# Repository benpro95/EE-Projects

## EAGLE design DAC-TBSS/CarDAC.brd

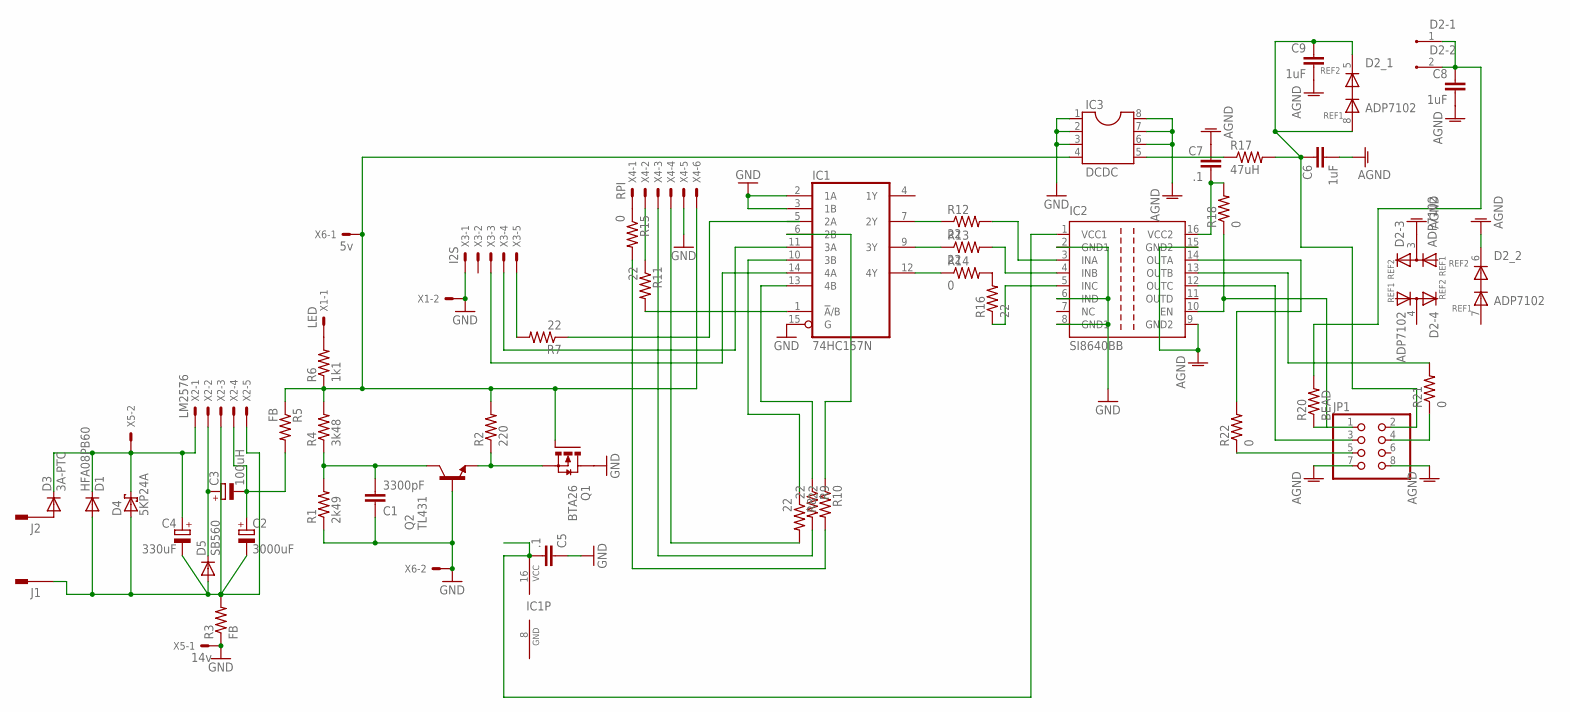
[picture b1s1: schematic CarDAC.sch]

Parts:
C1: 3300pF; C050-035X075
C2: 3000uF; E5-10,5
C3: 100uH; B45181C
C4: 330uF; E5-10,5
C5, C7: .1; C1210K
C6, C8, C9: 1uF; C1210K
D1: HFA08PB60; SOD57-10
D2: ADP7102; SO08
D3: 3A-PTC; SOD57-10
D4: 5KP24A; P6T15
D5: SB560; DO201-15
IC1: 74HC157N; DIL16
IC2: SI8640BB; SO-16DW
IC3: DCDC; DIL08
J1, J2: PIN2F061.040; F061.040
JP1: PINHD-2X4; 2X04
Q1: BTA26; TO247BV
Q2: TL431; TO92-EBC
R1: 2k49; 0309/10
R2: 220; 0309/10
R3: FB; 0309/10
R4: 3k48; 0309/10
R5: FB; 0309/12
R6: 1k1; 0309/10
R7, R9, R10, R11, R13: 22; 0309/12
R8, R16: 22; 0207/15
R12: 22; 0309/10
R14, R21: 0; 0207/15
R15: 0; 0309/12
R17: 47uH; 0309/10
R18, R22: 0; 0309/10
R20: BEAD; 0309/10
X1: LED; 22-23-2021
X2: LM2576; 22-23-2051
X3: I2S; 22-23-2051
X4: RPI; 22-23-2061
X5: 14v; 22-23-2021
X6: 5v; 22-23-2021

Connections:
AGND: C6.2, C7.1, C8.2, C9.2, D2.3 (K), D2.6 (REF2), IC2.9 (GND2), IC2.15 (GND2), IC3.6, IC3.7, IC3.8, JP1.7, JP1.8
GND: C1.1, C5.1, IC1.2 (1A), IC1.3 (1B), IC1.8 (GND), IC1.15 (G), IC2.2 (GND1), IC2.6 (IND), IC2.8 (GND1), IC3.1, IC3.2, IC3.3, Q1.D, Q2.B, R1.1, R3.1, X1.2, X3.1, X4.5, X5.1, X6.2
unnamed: Q1.S, Q2.E, R2.1
unnamed: IC3.4, Q1.G, R2.2, R4.2, R5.1, R6.1, X4.6, X6.1
unnamed: C1.2, Q2.C, R1.2, R4.1
unnamed: C4.+, D1.C, D3.C, D4.C, X2.1, X5.2
unnamed: D3.A, J2.A1, J2.A2
unnamed: C2.-, C4.-, D1.A, D4.A, D5.A, J1.A1, J1.A2, R3.2, X2.3, X2.5
unnamed: C3.+, D5.C, X2.2
unnamed: C2.+, C3.-, R5.2, X2.4
unnamed: R6.2, X1.1
unnamed: C5.2, IC1.16 (VCC), IC2.1 (VCC1)
unnamed: IC1.13 (4B), R9.1
unnamed: IC1.14 (4A), X3.3
unnamed: IC1.12 (4Y), R14.1
unnamed: IC1.10 (3B), R8.1
unnamed: IC1.11 (3A), X3.4
unnamed: IC1.6 (2B), R10.1
unnamed: IC1.5 (2A), R7.1
unnamed: R7.2, X3.5
unnamed: R10.2, R15.2
unnamed: IC1.1 (!A!/B), R11.2
unnamed: R9.2, X4.3
unnamed: R8.2, X4.4
unnamed: R11.1, X4.2
unnamed: IC1.7 (2Y), R12.1
unnamed: IC1.9 (3Y), R13.1
unnamed: R15.1, X4.1
unnamed: IC2.3 (INA), R12.2
unnamed: IC2.4 (INB), R13.2
unnamed: IC2.5 (INC), R16.1
unnamed: IC3.5, R17.1
unnamed: R14.2, R16.2
unnamed: C6.1, C9.1, D2.5 (REF2), D2.8 (REF1), JP1.2, R17.2
unnamed: IC2.10 (EN), JP1.1, R18.1, R20.1
unnamed: C8.1, D2.1 (K), D2.2 (K), R20.2
unnamed: IC2.12 (OUTC), JP1.3
unnamed: IC2.13 (OUTB), R21.2
unnamed: IC2.14 (OUTA), R22.2
unnamed: JP1.5, R22.1
unnamed: C7.2, IC2.16 (VCC2), R18.2
unnamed: JP1.4, R21.1

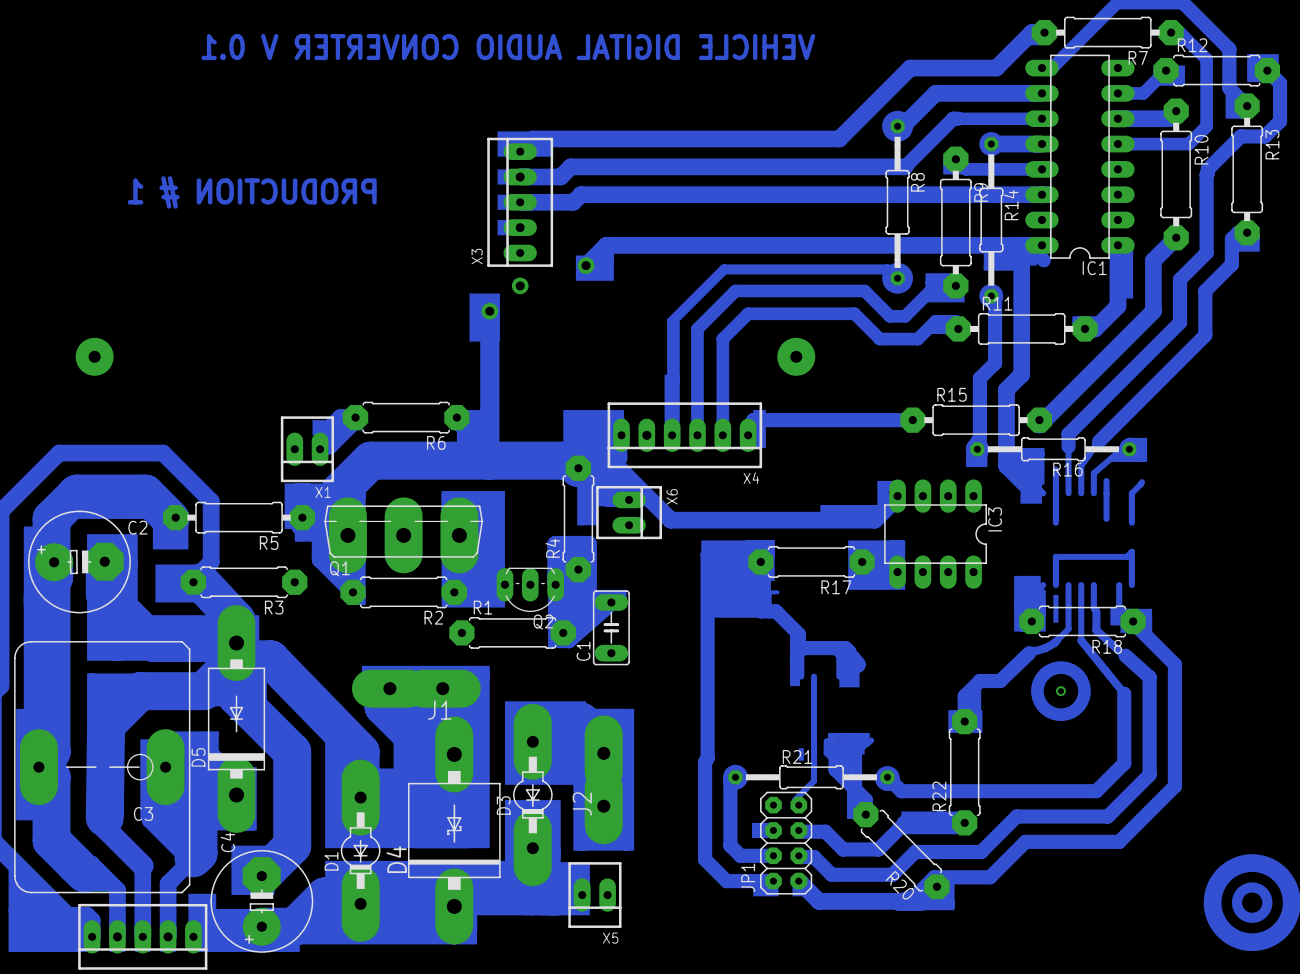
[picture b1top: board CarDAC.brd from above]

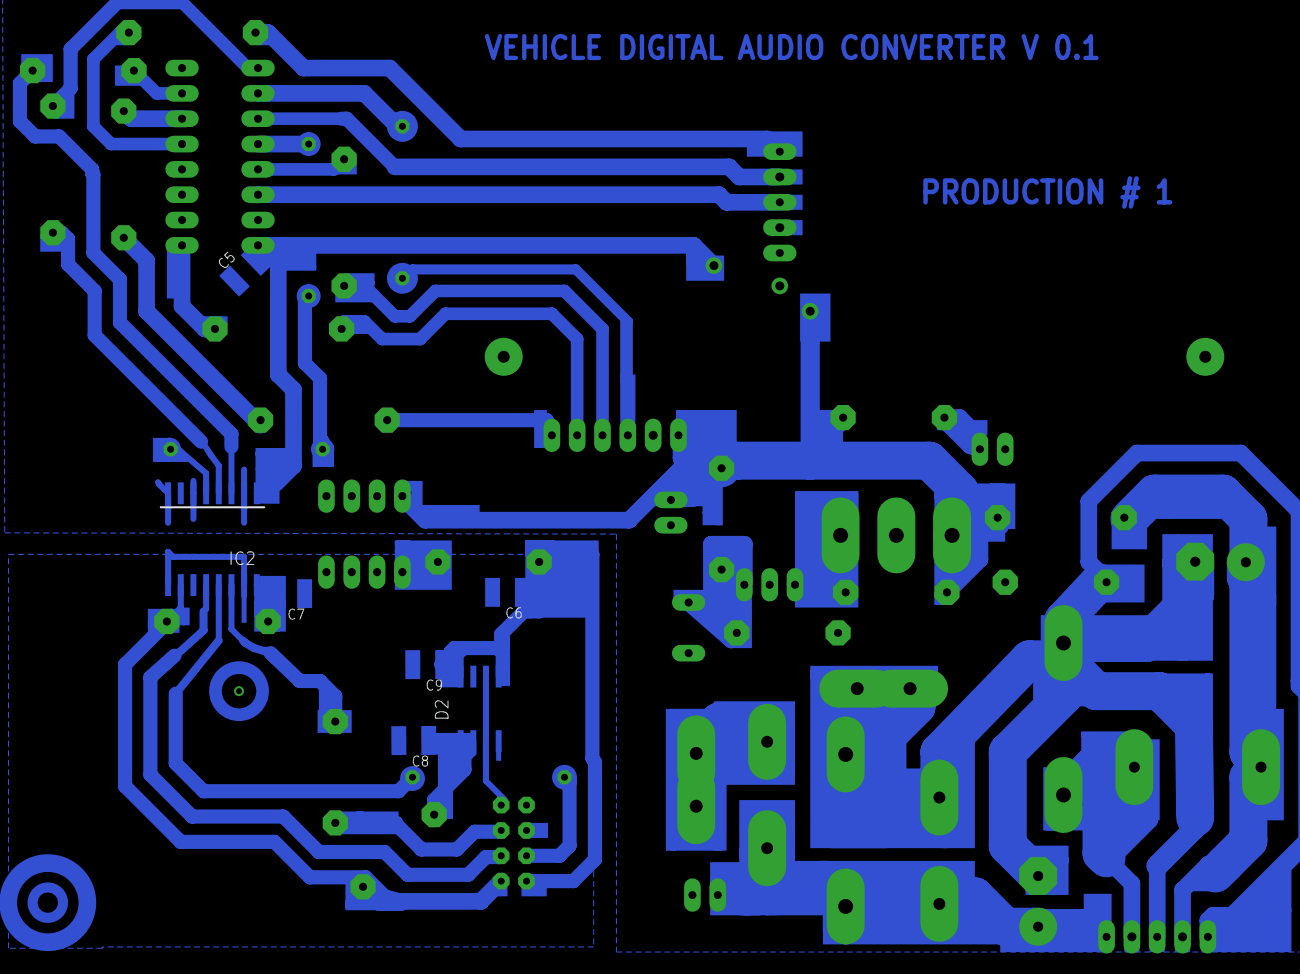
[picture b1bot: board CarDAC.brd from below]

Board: 2 copper layers, 49 parts (7 on the bottom side), 42 nets.

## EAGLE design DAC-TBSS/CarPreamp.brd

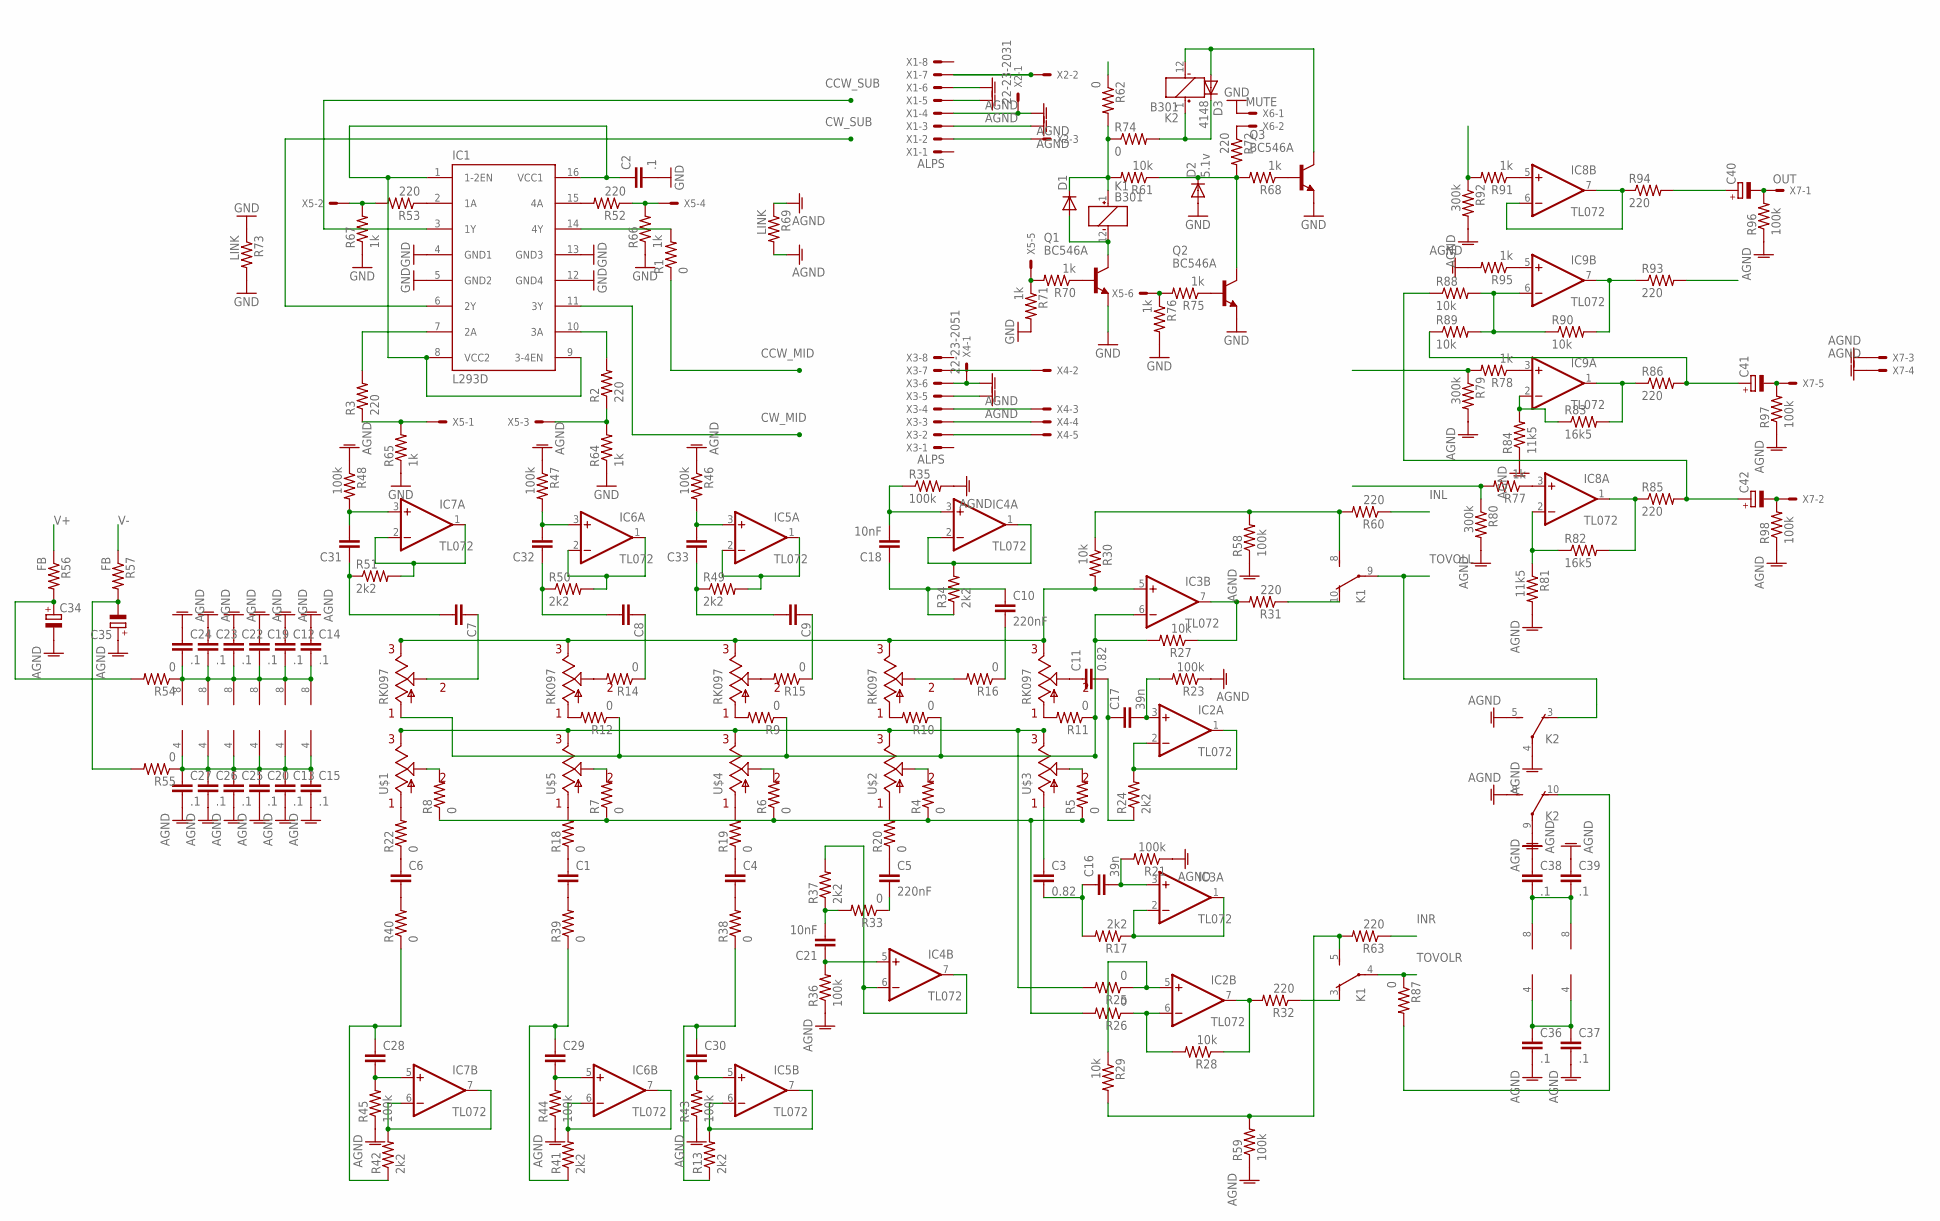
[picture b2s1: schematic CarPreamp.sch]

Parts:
C1, C4, C6, C7, C8, C9, C28, C29, C30, C31, C32, C33: C-EU050-035X075; C050-035X075
C2, C12, C13, C14, C15, C19, C20, C22, C23, C24, C25, C26, C27, C36, C37, C38, C39: .1; C1210
C3, C11: 0.82; C075-032X103
C5, C10: 220nF; C050-035X075
C16, C17: 39n; C050-035X075
C18, C21: 10nF; C050-035X075
C34, C35, C40, C41, C42: CPOL-EUE3.5-8; E3,5-8
D1: 1N4148DO35-10; DO35-10
D2: 5.1v; DO35-10
D3: 4148; DO35-10
IC1: L293D; DIL16
IC2, IC3, IC4, IC5, IC6, IC7, IC8, IC9: TL072; DIL08
K1, K2: B301; TXD2
Q1, Q2, Q3: BC546A; TO92-EBC
R1, R74: 0; 0309/12
R2: 220; 0309/12
R3: 220; 0207/15
R4, R5, R6, R7, R8, R9, R10, R11, R12, R14, R15, R16, R18, R19, R20, R22: 0; 0207/7
R13, R17, R24, R34, R37, R41, R42, R49, R50, R51: 2k2; 0207/7
R21, R23, R35, R36, R43, R44, R45, R46, R47, R48, R58, R59, R96, R97, R98: 100k; 0207/7
R25, R38, R39, R40, R87: 0; 0207/10
R26: 0; 0207/12
R27, R28, R61: 10k; R1210
R29, R88, R89, R90: 10k; 0207/7
R30: 10k; 0207/12
R31, R60, R63, R85, R86, R93, R94: 220; 0207/7
R32: 220; 0207/12
R33, R54, R62: 0; 0309/10
R52, R53: 220; 0309/10
R55: 0; 0411/15
R56, R57: FB; 0309/12
R64, R65, R66, R67, R68, R70, R71: 1k; R1210
R69: LINK; 0309/12
R72: 220; R1210
R73: LINK; 0309/10
R75, R76: 1k; 0309/10
R77, R78, R91: 1k; 0207/7
R79, R80, R92: 300k; 0207/7
R81, R84: 11k5; 0207/7
R82, R83: 16k5; 0207/7
R95: 1k; 0207/10
U$1, U$2, U$3, U$4, U$5: RK097; RK097-DUAL-ELEMENT
X1, X3: ALPS; 22-23-2081
X2: 22-23-2031
X4: 22-23-2051
X5: 22-23-2061
X6: MUTE; 22-23-2021
X7: OUT; 22-23-2051

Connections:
5V: C2.1, IC1.1 (1-2EN), IC1.8 (VCC2), IC1.9 (3-4EN), IC1.16 (VCC1), R62.1
AGND: C12.1, C13.2, C14.1, C15.2, C19.1, C20.2, C22.1, C23.1, C24.1, C25.2, C26.2, C27.2, C34.-, C35.+, C36.2, C37.2, C38.1, C39.1, K2.4, K2.5 (S), K2.8 (S), K2.9, R21.1, R23.1, R35.2, R36.1, R43.1, R44.1, R45.1, R46.1, R47.1, R48.1, R58.1, R59.1, R69.1, R69.2, R79.2, R80.2, R81.2, R84.1, R92.2, R95.2, R96.1, R97.1, R98.1, X1.3, X1.4, X1.5, X1.6, X2.1, X3.5, X3.6, X4.1, X7.3, X7.4
CCW_MID: R1.1
CCW_SUB: IC1.3 (1Y)
CW_MID: IC1.11 (3Y)
CW_SUB: IC1.6 (2Y)
GND: C2.2, D2.A, IC1.4 (GND1), IC1.5 (GND2), IC1.12 (GND4), IC1.13 (GND3), Q1.E, Q2.E, Q3.E, R64.1, R65.1, R66.1, R67.1, R71.2, R73.1, R73.2, R76.2, X6.1
INL: R60.1
INR: R63.1
unnamed: IC1.14 (4Y), R1.2
unnamed: X3.2, X4.5
unnamed: X3.3, X4.4
unnamed: IC1.7 (2A), R3.2
unnamed: IC1.15 (4A), R52.2
unnamed: X1.2, X2.3
unnamed: X1.7, X2.2
unnamed: IC1.10 (3A), R2.2
unnamed: X3.7, X4.2
unnamed: R25.2, U$1.P$4 (E1), U$2.P$4 (E1), U$3.P$4 (E1), U$4.P$4 (E1), U$5.P$4 (E1)
unnamed: IC3.5 (+IN), R30.2, U$1.P$3 (E), U$2.P$3 (E), U$3.P$3 (E), U$4.P$3 (E), U$5.P$3 (E)
unnamed: X3.4, X4.3
unnamed: R5.2, U$3.P$6 (S1)
unnamed: R6.2, U$4.P$6 (S1)
unnamed: R7.2, U$5.P$6 (S1)
unnamed: R8.2, U$1.P$6 (S1)
unnamed: R4.1, R5.1, R6.1, R7.1, R8.1, R26.2
unnamed: R16.2, U$2.P$5 (S)
unnamed: R4.2, U$2.P$6 (S1)
unnamed: R9.2, U$4.P$1 (A)
unnamed: R10.2, U$2.P$1 (A)
unnamed: R11.2, U$3.P$1 (A)
unnamed: R12.2, U$5.P$1 (A)
unnamed: IC7.6 (-IN), IC7.7 (OUT), R42.2
unnamed: IC3.6 (-IN), R9.1, R10.1, R11.1, R12.1, R27.2, U$1.P$1 (A)
unnamed: R14.2, U$5.P$5 (S)
unnamed: R15.2, U$4.P$5 (S)
unnamed: C11.1, U$3.P$5 (S)
unnamed: R18.2, U$5.P$2 (A1)
unnamed: R19.2, U$4.P$2 (A1)
unnamed: R20.2, U$2.P$2 (A1)
unnamed: C3.1, U$3.P$2 (A1)
unnamed: R22.2, U$1.P$2 (A1)
unnamed: C1.1, R18.1
unnamed: IC6.6 (-IN), IC6.7 (OUT), R41.2
unnamed: C4.1, R19.1
unnamed: C5.1, R20.1
unnamed: C6.1, R22.1
unnamed: C7.1, U$1.P$5 (S)
unnamed: C8.1, R14.1
unnamed: C9.1, R15.1
unnamed: C10.2, R16.1
unnamed: IC5.6 (-IN), IC5.7 (OUT), R13.2
unnamed: IC2.5 (+IN), R25.1, R29.1
unnamed: IC2.6 (-IN), R26.1, R28.2
unnamed: IC3.7 (OUT), R27.1, R31.2
unnamed: IC2.7 (OUT), R28.1, R32.2
unnamed: IC4.1 (OUT), IC4.2 (-IN), R34.2
unnamed: C10.1, C18.1, R34.1
unnamed: IC4.6 (-IN), IC4.7 (OUT), R37.2
unnamed: IC2.1 (OUT), IC2.2 (-IN), R24.2
unnamed: IC3.1 (OUT), IC3.2 (-IN), R17.1
unnamed: C16.2, IC3.3 (+IN), R21.2
unnamed: C3.2, C16.1, R17.2
unnamed: C17.2, IC2.3 (+IN), R23.2
unnamed: C11.2, C17.1, R24.1
unnamed: C5.2, R33.1
unnamed: C18.2, IC4.3 (+IN), R35.1
unnamed: C21.2, R33.2, R37.1
unnamed: C21.1, IC4.5 (+IN), R36.2
unnamed: C12.2, C14.2, C19.2, C22.2, C23.2, C24.2, IC2.8 (V+), IC3.8 (V+), IC4.8 (V+), IC5.8 (V+), IC6.8 (V+), IC7.8 (V+), R54.1
unnamed: C28.2, IC7.5 (+IN), R45.2
unnamed: C29.2, IC6.5 (+IN), R44.2
unnamed: C30.2, IC5.5 (+IN), R43.2
unnamed: C28.1, R40.1, R42.1
unnamed: C13.1, C15.1, C20.1, C25.1, C26.1, C27.1, IC2.4 (V-), IC3.4 (V-), IC4.4 (V-), IC5.4 (V-), IC6.4 (V-), IC7.4 (V-), R55.1
unnamed: C4.2, R38.2
unnamed: C1.2, R39.2
unnamed: C6.2, R40.2
unnamed: C29.1, R39.1, R41.1
unnamed: C30.1, R13.1, R38.1
unnamed: IC7.1 (OUT), IC7.2 (-IN), R51.2
unnamed: IC6.1 (OUT), IC6.2 (-IN), R50.2
unnamed: IC5.1 (OUT), IC5.2 (-IN), R49.2
unnamed: C7.2, C31.1, R51.1
unnamed: C8.2, C32.1, R50.1
unnamed: C9.2, C33.1, R49.1
unnamed: C31.2, IC7.3 (+IN), R48.2
unnamed: C32.2, IC6.3 (+IN), R47.2
unnamed: C33.2, IC5.3 (+IN), R46.2
unnamed: IC1.2 (1A), R53.1
unnamed: Q1.B, R70.1
unnamed: R70.2, R71.1, X5.5
unnamed: K1.10 (O), R31.1
unnamed: K1.8 (S), R30.1, R58.2, R60.2
unnamed: K1.5 (S), R29.2, R59.2, R63.2
unnamed: K1.3 (O), R32.1
unnamed: R3.1, R65.2, X5.1
unnamed: R2.1, R64.2, X5.3
unnamed: D1.C, K1.1 (+), R61.2, R62.2, R74.1
unnamed: D1.A, K1.12 (-), Q1.C
unnamed: R52.1, R66.2, X5.4
unnamed: R53.2, R67.2, X5.2
unnamed: D2.C, Q2.C, R61.1, R68.2, R72.2
unnamed: Q2.B, R75.1
unnamed: R75.2, R76.1, X5.6
unnamed: Q3.B, R68.1
unnamed: R72.1, X6.2
unnamed: D3.C, K2.1 (+), R74.2
unnamed: D3.A, K2.12 (-), Q3.C
unnamed: C38.2, C39.2, IC8.8 (V+), IC9.8 (V+)
unnamed: C36.1, C37.1, IC8.4 (V-), IC9.4 (V-)
unnamed: IC9.1 (OUT), R83.2, R86.1
unnamed: IC8.1 (OUT), R82.2, R85.1
unnamed: IC8.6 (-IN), IC8.7 (OUT), R94.1
unnamed: IC9.7 (OUT), R90.2, R93.1
unnamed: IC8.3 (+IN), R77.1
unnamed: IC9.3 (+IN), R78.1
unnamed: R78.2, R79.1
unnamed: R77.2, R80.1
unnamed: IC9.2 (-IN), R83.1, R84.2
unnamed: IC8.2 (-IN), R81.1, R82.1
unnamed: IC9.6 (-IN), R88.2, R89.2, R90.1
unnamed: K2.10 (O), R87.2
unnamed: IC8.5 (+IN), R91.1
unnamed: R91.2, R92.1
unnamed: IC9.5 (+IN), R95.1
unnamed: C41.+, R86.2, R89.1
unnamed: C42.+, R85.2, R88.1
unnamed: C40.+, R94.2
unnamed: C40.-, R96.2, X7.1
unnamed: C41.-, R97.2, X7.5
unnamed: C42.-, R98.2, X7.2
TOVOLL: K1.9, K2.3 (O)
TOVOLR: K1.4, R87.1
V+: R56.1
V++: C34.+, R54.2, R56.2
V-: R57.1
V--: C35.-, R55.2, R57.2

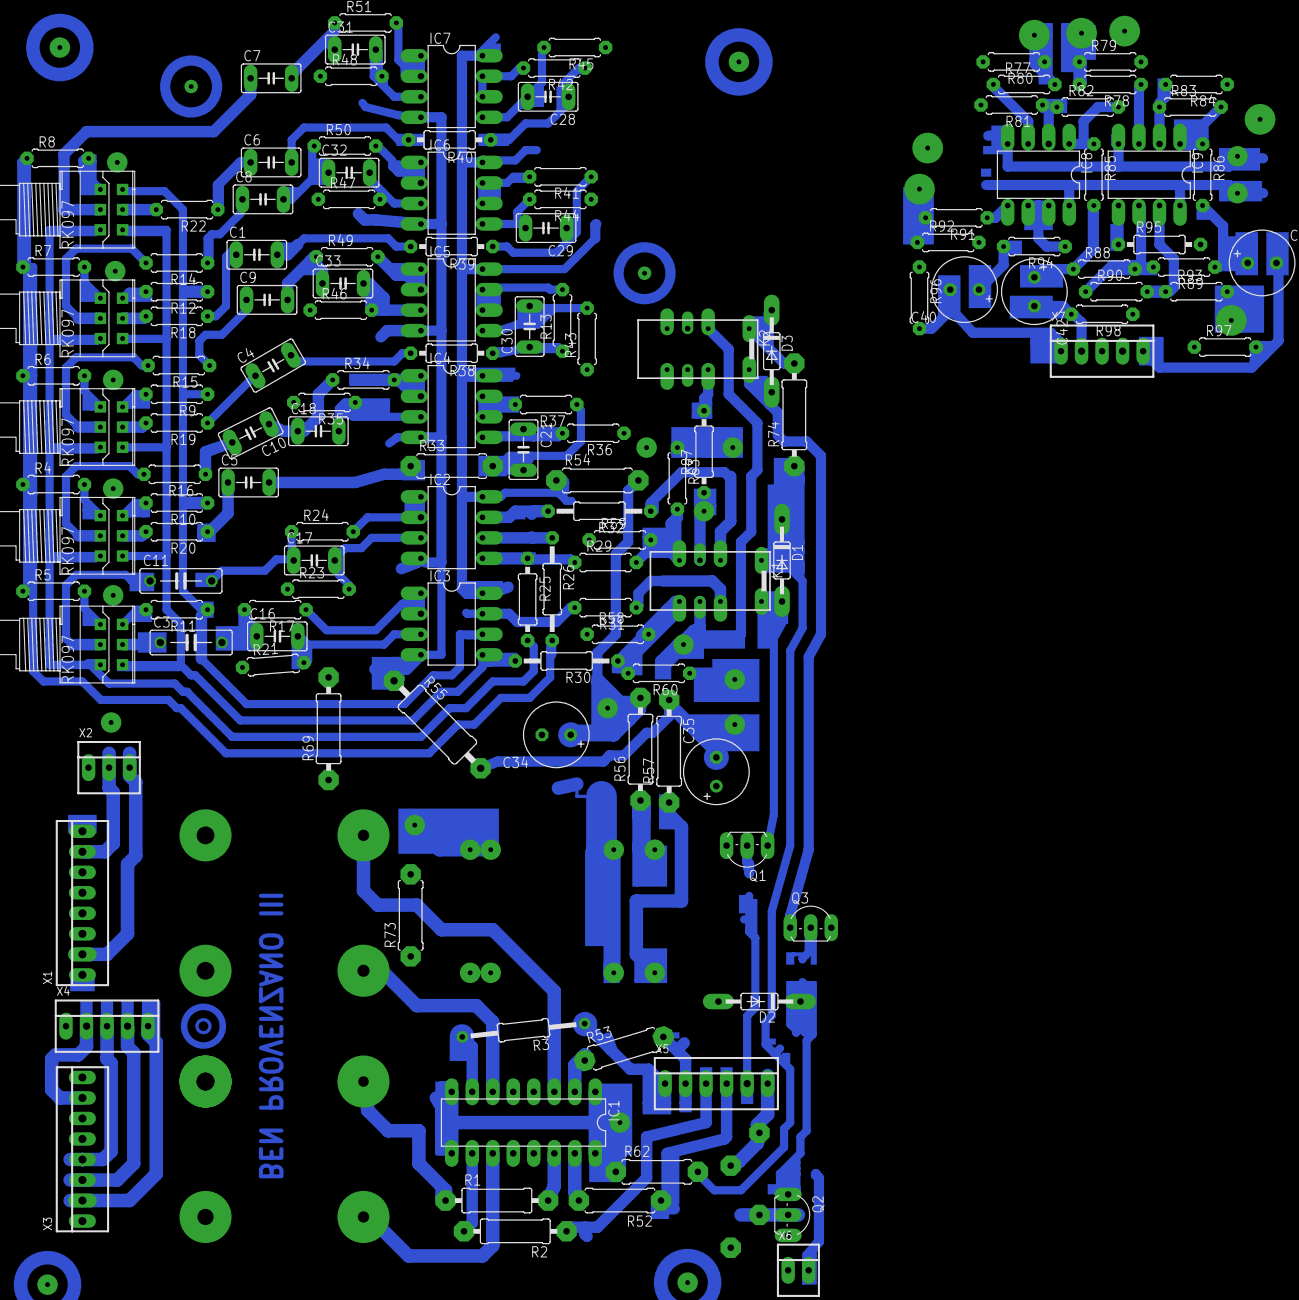
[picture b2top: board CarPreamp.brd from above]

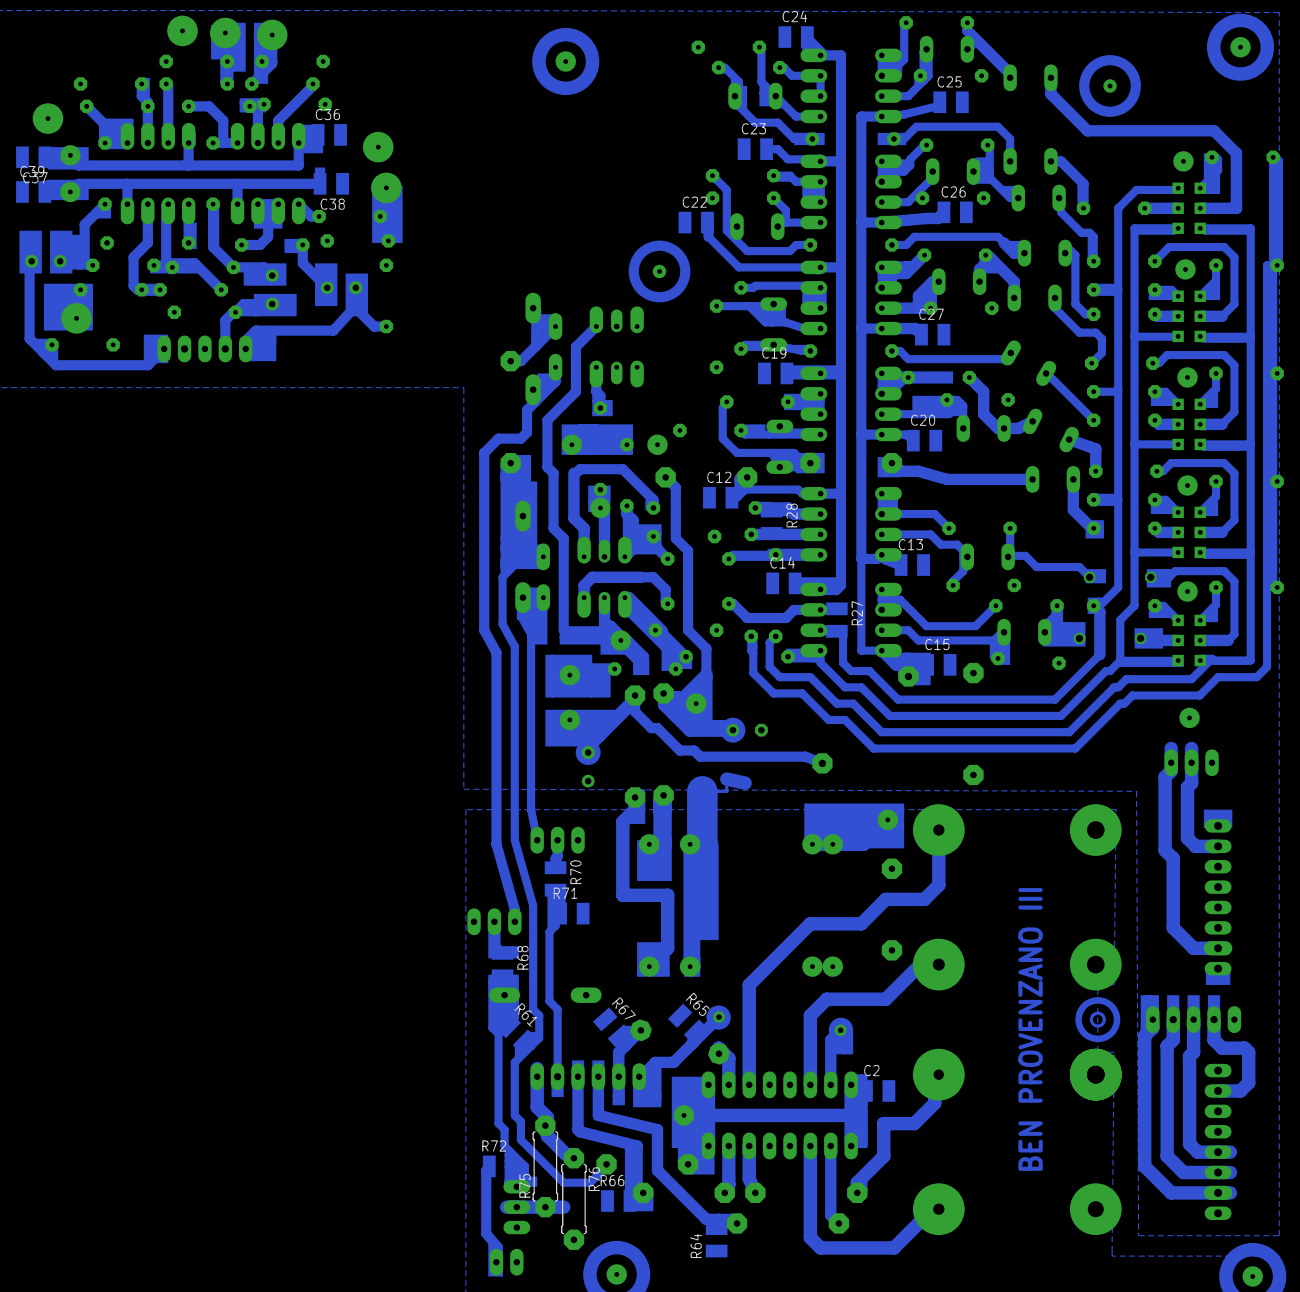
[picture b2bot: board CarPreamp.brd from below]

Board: 2 copper layers, 169 parts (30 on the bottom side), 130 nets.

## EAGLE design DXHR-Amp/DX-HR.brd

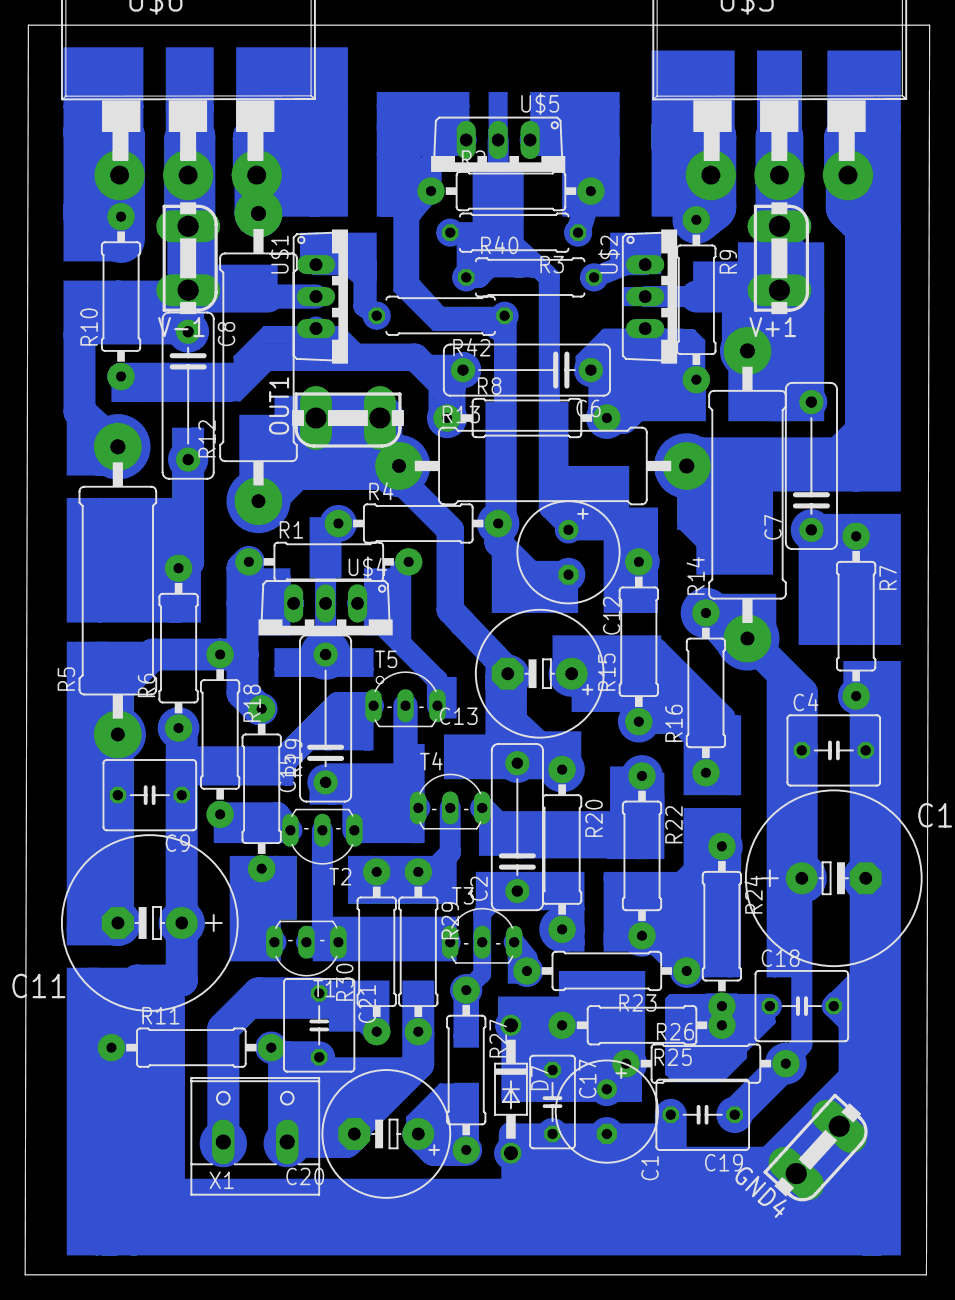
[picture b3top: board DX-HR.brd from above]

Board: 2 copper layers, 71.9 x 99.3 mm, 63 parts (0 on the bottom side), 36 nets.

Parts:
C1: 2u2; E3,5-8
C2: 10pF; C102-043X133
C4, C9: 68nF; C050-055X075
C6: 220nF; C102-043X133
C7, C8: 68nF; C102-043X133
C10, C11: 470uF; E5-13
C12: 2.2uF; E3,5-8
C13: 100uF; E5-10,5
C15: 150pF; C102-043X133
C17: 68nF; C050-035X075
C18: 2n7; C050-055X075
C19: 10nF; C050-055X075
C20: 470uF; E5-10,5
C21: 220pF; C050-055X075
D7: 12V; DO41-10
GND4: GND; FASTON
OUT1: QFIT; FASTON
R1: 1K2; 0309/12
R2: 720R; 0309/12
R3: 2K2; 0309/10
R4, R6, R7: 0R; 0309/12
R5: 470R; 0617/22
R8: 220R; 0309/12
R9, R10: 5R6; 0309/12
R11: 10R; 0309/12
R12, R13: .22; 0617/22
R14: 270R; 0617/22
R15, R26: 3K3; 0309/12
R16: 2K2; 0309/12
R18, R19: 47R; 0309/12
R20, R29: 12K; 0309/12
R22, R23: 100R; 0309/12
R24: 3K6; 0309/12
R25: 4K7; 0309/12
R27: 330R; 0309/12
R30: 150R; 0309/12
R40, R42: 100R; 0309/10
T1, T2, T5: BC546B; TO92-CBE
T3, T4: BC556A; TO92-CBE
U$1: A1220AYS; TO220AV
U$2, U$4: C2690AYS; TO220AV
U$3: C5200OTU; TO-264
U$5: BD13916; TO220AV
U$6: A1943OTU; TO-264
V+1: QFIT; FASTON
V-1: QFIT; FASTON
X1: W237-132

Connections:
AGND: C20.-, C21.2, R11.2, R29.2, X1.2
unnamed: R1.2, T5.E, U$4.B
unnamed: R2.2, R3.1, U$5.B
unnamed: C8.2, R6.2
unnamed: C12.+, R3.2, R15.2, R40.1, U$5.C
unnamed: R40.2, U$2.B
unnamed: C7.2, R14.2, U$2.C, U$3.C, V+1.1, V+1.2
unnamed: C12.-, R2.1, R4.2, R42.1, U$5.E
unnamed: C15.2, R4.1, U$4.C
unnamed: R42.2, U$1.B
unnamed: C6.2, R8.1, R10.1, U$1.E
unnamed: C7.1, R7.1
unnamed: C6.1, R8.2, R9.2, U$2.E
unnamed: C8.1, R5.2, U$1.C, U$6.C, V-1.1, V-1.2
unnamed: R9.1, U$3.B
unnamed: R10.2, U$6.B
unnamed: C9.2, C11.-, R1.1, R5.1, R18.1, R19.1, U$4.E
unnamed: R12.2, U$6.E
unnamed: R13.2, U$3.E
unnamed: C4.1, C10.+, C19.1, R14.1, R16.2, R26.2
unnamed: R29.1, R30.2, T4.B
unnamed: C21.1, R30.1, X1.1
unnamed: C13.+, R15.1, R16.1
unnamed: C2.1, R20.2, R27.1, T3.B
unnamed: R18.2, T2.E
unnamed: T1.B, T1.C, T2.B, T3.C
unnamed: R22.1, T4.E
unnamed: C15.1, T2.C, T4.C, T5.B
unnamed: R19.2, T1.E
unnamed: R23.2, T3.E
unnamed: R22.2, R23.1, R24.1
unnamed: C18.1, R24.2, R25.1
unnamed: C1.+, C17.1, D7.C, R25.2, R26.1
unnamed: C20.+, R27.2
PE: C1.-, C4.2, C9.1, C10.-, C11.+, C17.2, C18.2, C19.2, D7.A, GND4.1, GND4.2, R6.1, R7.2, R11.1, T5.C
VCCIO: C2.2, C13.-, OUT1.1, OUT1.2, R12.1, R13.1, R20.1

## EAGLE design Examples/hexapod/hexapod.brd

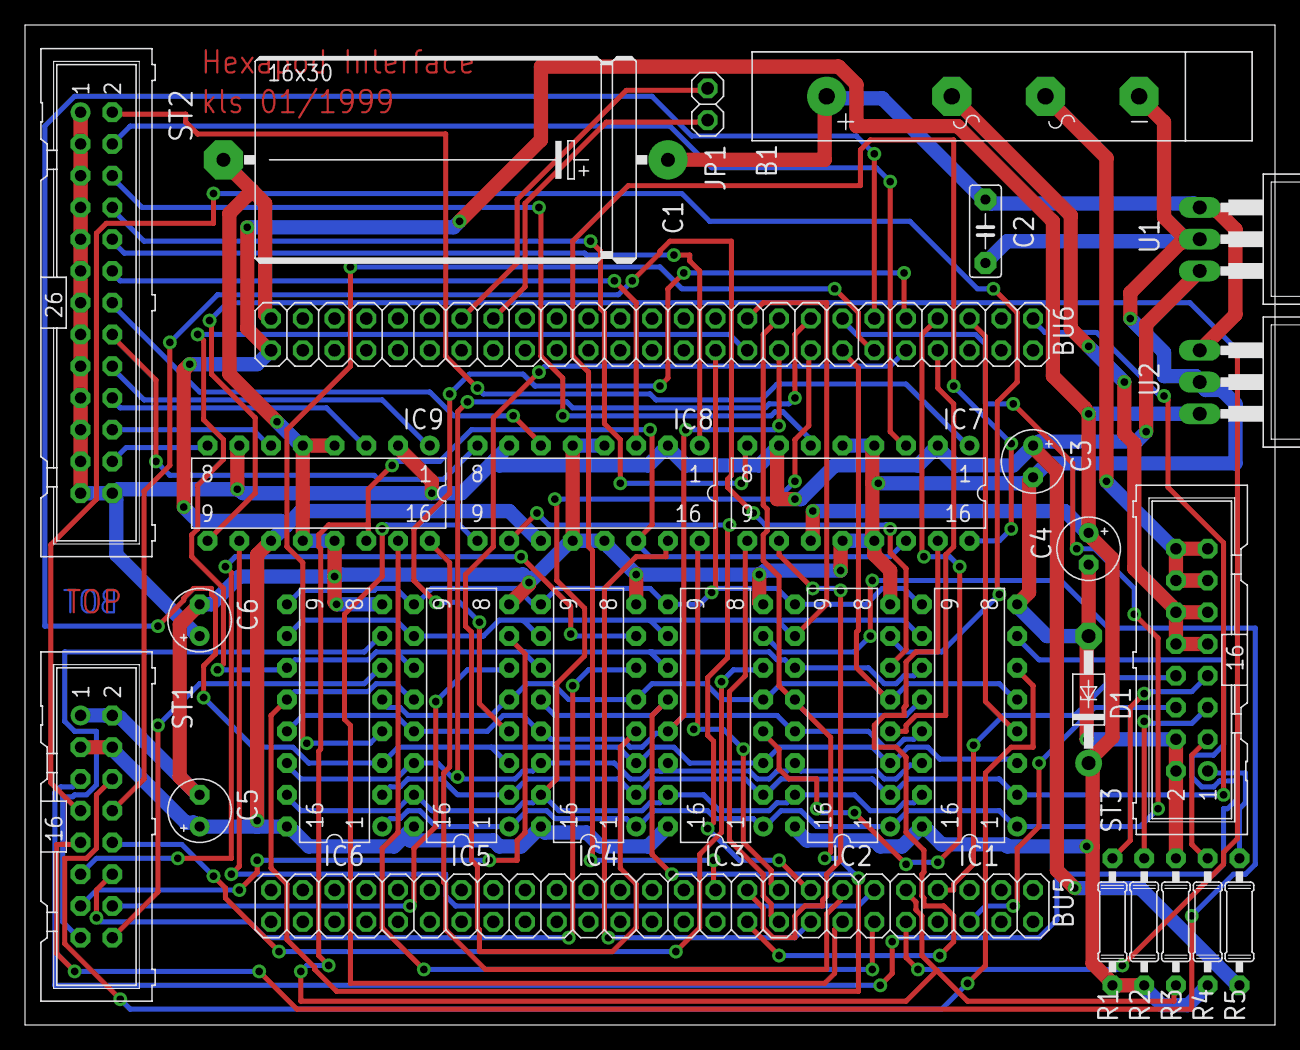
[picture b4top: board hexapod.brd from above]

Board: 2 copper layers, 100.0 x 80.0 mm, 30 parts (0 on the bottom side), 68 nets.

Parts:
B1: FB100
BU5, BU6: PINHD-2X25; 2X25
C1: 2200uF/35V; E35-16
C2: 100nf; C5B2,5A
C3, C6: 4,7uf/35V; E2,5-5
C4, C5: 4,7uf/10V; E2,5-5
D1: BZX85; DO41Z10
IC1, IC2, IC3, IC4, IC5, IC6: HCTL2016; DIL-16
IC7, IC8, IC9: DS3668; DIL-16
JP1: PINHD-1X2; 1X02
R1, R2, R4, R5: 0207/10
R3: 10k; 0207/10@1
ST1, ST3: PINHD-2X8; ML16
ST2: PINHD-2X13; ML26
U1: 78S24; TO220H
U2: 7805; TO220H

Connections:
!OE0: BU6.5, IC1.4
!OE1: BU6.8, IC2.4
!OE2: BU6.7, IC3.4
!OE3: BU6.10, IC4.4
!OE4: BU6.9, IC5.4
!OE5: BU6.12, IC6.4
!RST: BU6.14, IC1.5, IC2.5, IC3.5, IC4.5, IC5.5, IC6.5
+5V: BU6.50, C4.+, C5.+, D1.K, IC1.16, IC2.16, IC3.16, IC4.16, IC5.16, IC6.16, IC7.11, IC8.11, IC9.11, R1.1, R2.1, R4.1, ST1.3, ST1.4, U2.3
+24V: C3.+, C6.+, IC7.2, IC7.7, IC8.2, IC8.7, IC9.2, IC9.7, R5.1, ST2.1, ST2.3, ST2.5, ST2.7, ST2.9, ST2.11, ST2.13, ST2.15, ST2.17, ST2.19, ST2.21, ST2.23, ST2.25, ST2.26, U1.3
AC1: B1.AC1, ST3.9, ST3.10, ST3.11, ST3.12
AC2: B1.AC2, ST3.13, ST3.14, ST3.15, ST3.16
CLK: BU6.1, IC1.2, IC2.2, IC3.2, IC4.2, IC5.2, IC6.2
COIL0: IC7.1, ST2.2
COIL1: IC7.3, ST2.4
COIL2: IC7.6, ST2.6
COIL3: IC7.8, ST2.8
COIL4: IC8.1, ST2.10
COIL5: IC8.3, ST2.12
COIL6: IC8.6, ST2.14
COIL7: IC8.8, ST2.16
COIL8: IC9.1, ST2.18
COIL9: IC9.3, ST2.20
COIL10: IC9.6, ST2.22
COIL11: IC9.8, ST2.24
D0: BU6.13, IC1.1, IC2.1, IC3.1, IC4.1, IC5.1, IC6.1
D1: BU6.16, IC1.15, IC2.15, IC3.15, IC4.15, IC5.15, IC6.15
D2: BU6.15, IC1.14, IC2.14, IC3.14, IC4.14, IC5.14, IC6.14
D3: BU6.18, IC1.13, IC2.13, IC3.13, IC4.13, IC5.13, IC6.13
D4: BU6.17, IC1.12, IC2.12, IC3.12, IC4.12, IC5.12, IC6.12
D5: BU6.20, IC1.11, IC2.11, IC3.11, IC4.11, IC5.11, IC6.11
D6: BU6.19, IC1.10, IC2.10, IC3.10, IC4.10, IC5.10, IC6.10
D7: BU6.22, IC1.9, IC2.9, IC3.9, IC4.9, IC5.9, IC6.9
EN: BU5.9, IC7.14, IC8.14, IC9.14, R3.2
ENC0: IC1.7, ST1.5
ENC1: IC1.6, ST1.6
ENC2: IC2.7, ST1.7
ENC3: IC2.6, ST1.8
ENC4: IC3.7, ST1.9
ENC5: IC3.6, ST1.10
ENC6: IC4.7, ST1.11
ENC7: IC4.6, ST1.12
ENC8: IC5.7, ST1.13
ENC9: IC5.6, ST1.14
ENC10: IC6.7, ST1.15
ENC11: IC6.6, ST1.16
GND: B1.-, BU6.49, C1.-, C2.1, C3.-, C4.-, C5.-, C6.-, D1.A, IC1.8, IC2.8, IC3.8, IC4.8, IC5.8, IC6.8, IC7.4, IC7.5, IC7.12, IC7.13, IC8.4, IC8.5, IC8.12, IC8.13, IC9.4, IC9.5, IC9.12, IC9.13, R3.1, ST1.1, ST1.2, ST3.2, ST3.4, U1.2, U2.2
unnamed: R5.2, ST3.1
unnamed: R4.2, ST3.3
unnamed: R2.2, ST3.5
unnamed: R1.2, ST3.7
unnamed: BU6.35, JP1.2
unnamed: BU6.37, JP1.1
SEL: BU6.11, IC1.3, IC2.3, IC3.3, IC4.3, IC5.3, IC6.3
STATUS0: BU5.7, ST3.8
STATUS1: BU5.6, ST3.6
VALVE0: BU5.21, IC7.16
VALVE1: BU5.20, IC7.15
VALVE2: BU5.19, IC7.10
VALVE3: BU5.18, IC7.9
VALVE4: BU5.17, IC8.16
VALVE5: BU5.16, IC8.15
VALVE6: BU5.15, IC8.10
VALVE7: BU5.14, IC8.9
VALVE8: BU5.13, IC9.16
VALVE9: BU5.12, IC9.15
VALVE10: BU5.11, IC9.10
VALVE11: BU5.10, IC9.9
VIN: B1.+, C1.+, C2.2, U1.1, U2.1
